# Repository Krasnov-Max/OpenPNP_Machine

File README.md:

# OpenPNP_Machine

Pick and Place small machine. 

Making parts machine if FreeCAD
Add configure files for RepRap firmware and OpenPNP

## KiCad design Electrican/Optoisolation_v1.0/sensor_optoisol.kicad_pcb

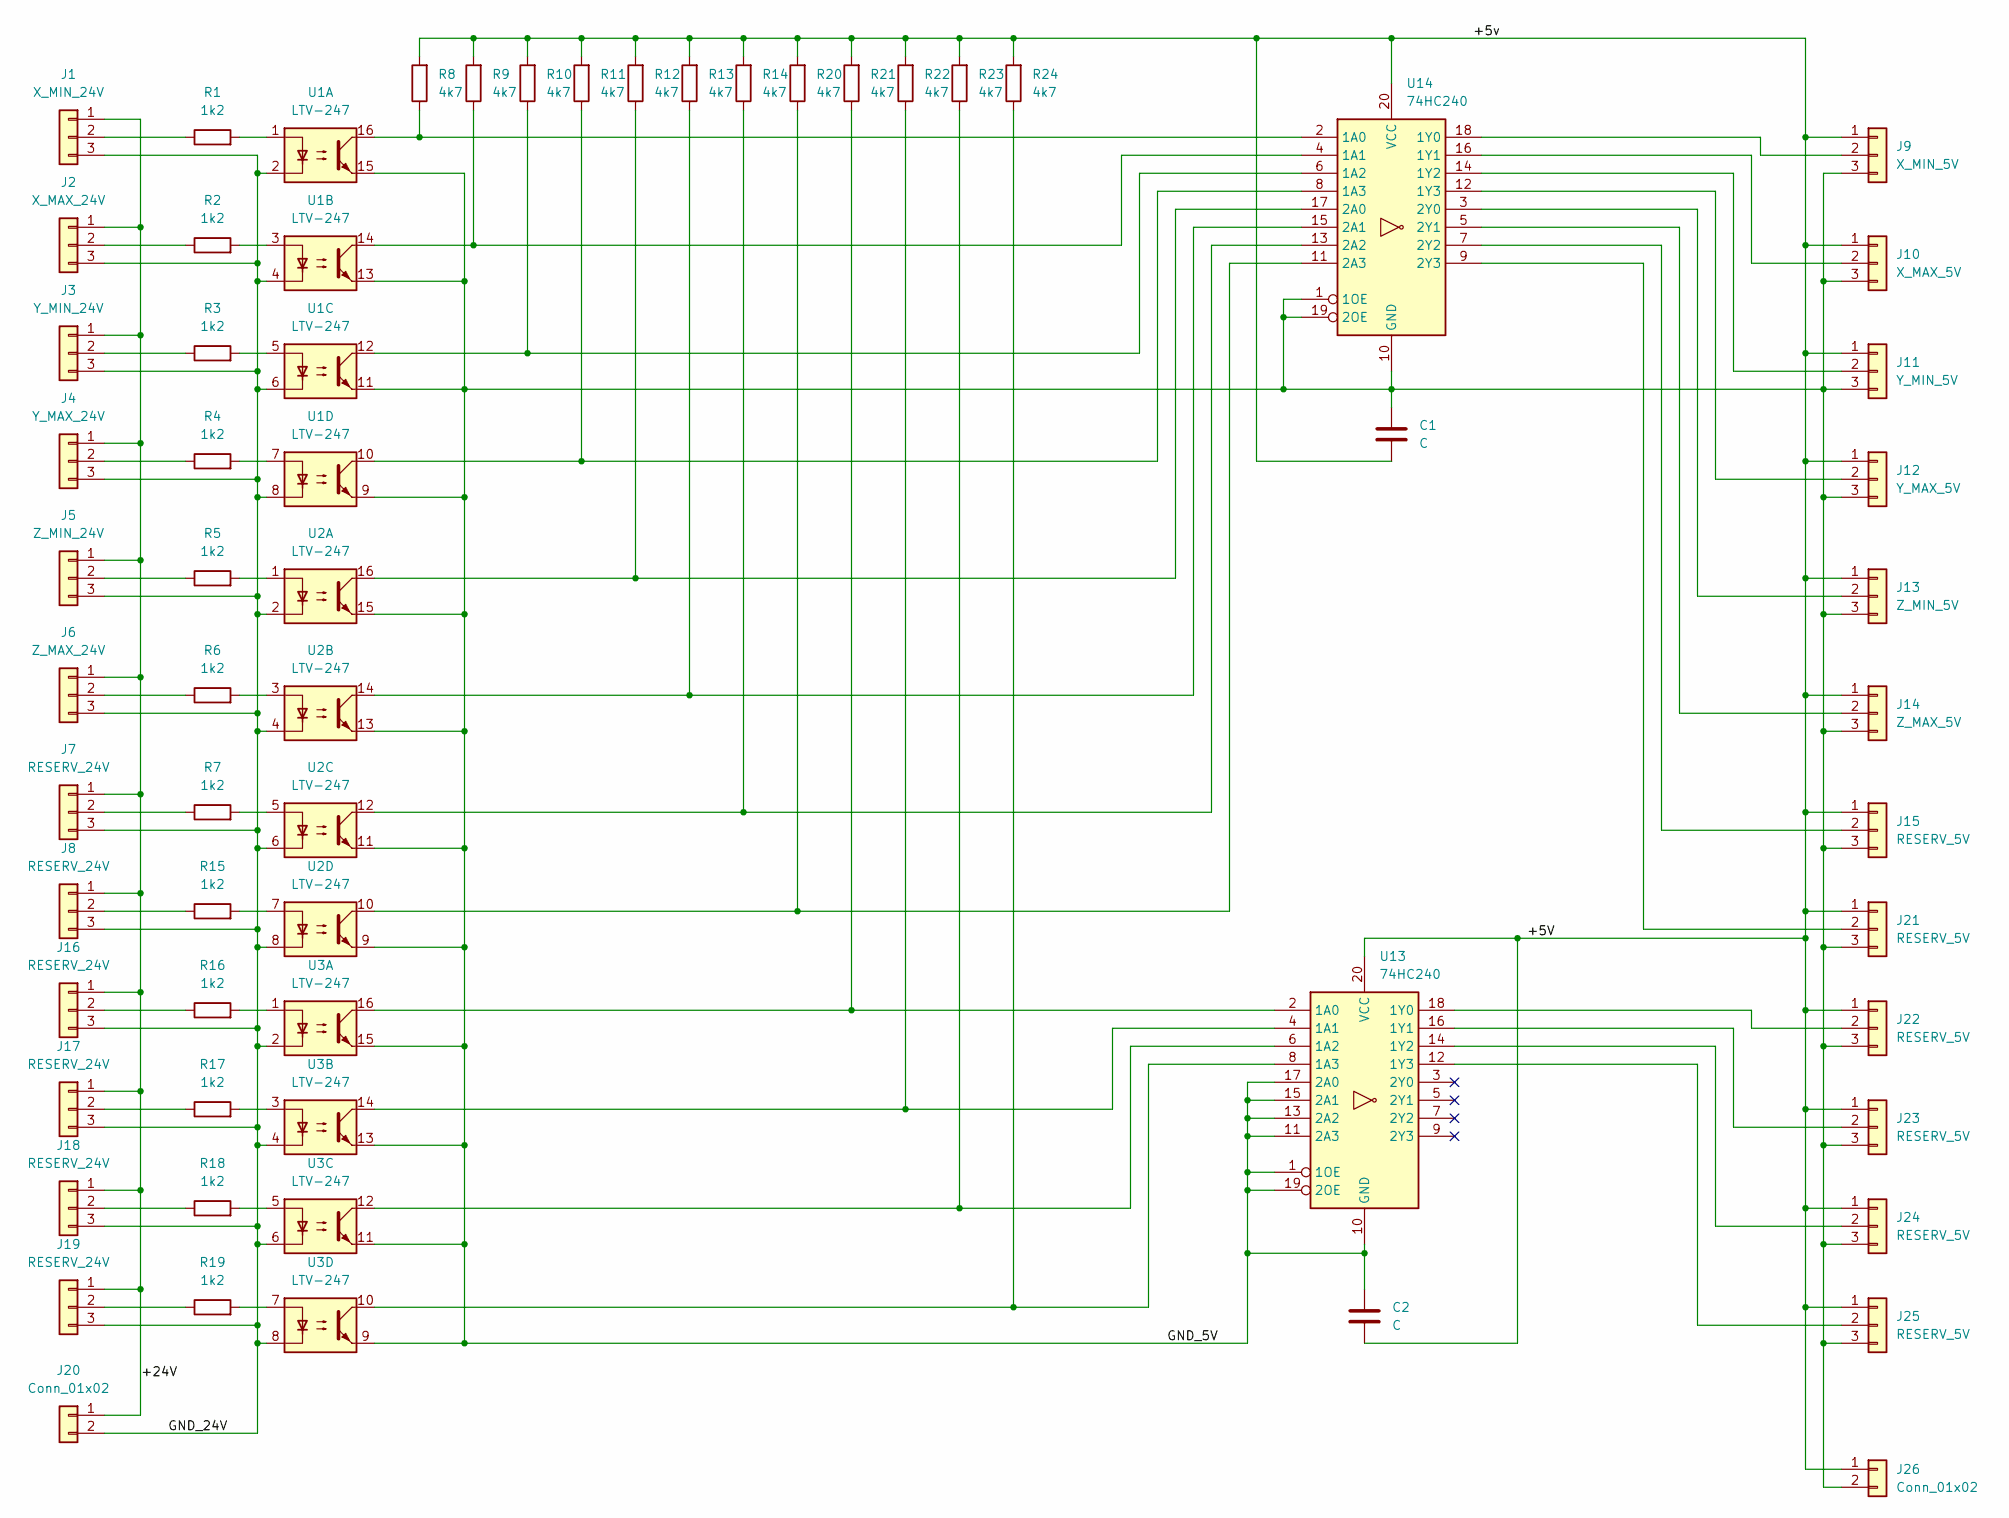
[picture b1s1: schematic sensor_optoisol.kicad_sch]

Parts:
C1, C2: C; C_0805_2012Metric
J1: Conn_01x03; Molex_SL_171971-0003_1x03_P2.54mm_Vertical
J2: X_MAX_24V; Molex_SL_171971-0003_1x03_P2.54mm_Vertical
J3: Y_MIN_24V; Molex_SL_171971-0003_1x03_P2.54mm_Vertical
J4: Y_MAX_24V; Molex_SL_171971-0003_1x03_P2.54mm_Vertical
J5: Z_MIN_24V; Molex_SL_171971-0003_1x03_P2.54mm_Vertical
J6: Z_MAX_24V; Molex_SL_171971-0003_1x03_P2.54mm_Vertical
J7, J8, J16, J17, J18, J19: RESERV_24V; Molex_SL_171971-0003_1x03_P2.54mm_Vertical
J9: X_MIN_5V; Molex_SL_171971-0003_1x03_P2.54mm_Vertical
J10: X_MAX_5V; Molex_SL_171971-0003_1x03_P2.54mm_Vertical
J11: Y_MIN_5V; Molex_SL_171971-0003_1x03_P2.54mm_Vertical
J12: Y_MAX_5V; Molex_SL_171971-0003_1x03_P2.54mm_Vertical
J13: Z_MIN_5V; Molex_SL_171971-0003_1x03_P2.54mm_Vertical
J14: Z_MAX_5V; Molex_SL_171971-0003_1x03_P2.54mm_Vertical
J15, J21, J22, J23, J24, J25: RESERV_5V; Molex_SL_171971-0003_1x03_P2.54mm_Vertical
J20, J26: Conn_01x02; Molex_SL_171971-0002_1x02_P2.54mm_Vertical
R1, R2, R3, R4, R5, R6, R7, R15, R16, R17, R18, R19: 1k2; R_0805_2012Metric_Pad1.20x1.40mm_HandSolder
R8, R9, R10, R11, R12, R13, R14, R20, R21, R22, R23, R24: 4k7; R_0805_2012Metric_Pad1.20x1.40mm_HandSolder
U1, U2, U3: LTV-247; SOIC-16W_5.3x10.2mm_P1.27mm
U13, U14: 74HC240; SOIC-20W_7.5x12.8mm_P1.27mm

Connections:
/+5V: C1.2, C2.2, J9.1, J10.1, J11.1, J12.1, J13.1, J14.1, J15.1, J21.1, J22.1, J23.1, J24.1, J25.1, J26.1, R8.2, R9.2, R10.2, R11.2, R12.2, R13.2, R14.2, R20.2, R21.2, R22.2, R23.2, R24.2, U13.20 (VCC), U14.20 (VCC)
/+24V: J1.1, J2.1, J3.1, J4.1, J5.1, J6.1, J7.1, J8.1, J16.1, J17.1, J18.1, J19.1, J20.1
/GND_5V: C1.1, C2.1, J9.3, J10.3, J11.3, J12.3, J13.3, J14.3, J15.3, J21.3, J22.3, J23.3, J24.3, J25.3, J26.2, U1.9, U1.11, U1.13, U1.15, U2.9, U2.11, U2.13, U2.15, U3.9, U3.11, U3.13, U3.15, U13.1 (1OE), U13.10 (GND), U13.11 (2A3), U13.13 (2A2), U13.15 (2A1), U13.17 (2A0), U13.19 (2OE), U14.1 (1OE), U14.10 (GND), U14.19 (2OE)
/GND_24V: J1.3, J2.3, J3.3, J4.3, J5.3, J6.3, J7.3, J8.3, J16.3, J17.3, J18.3, J19.3, J20.2, U1.2, U1.4, U1.6, U1.8, U2.2, U2.4, U2.6, U2.8, U3.2, U3.4, U3.6, U3.8
unnamed: J1.2, R1.1
unnamed: J2.2, R2.1
unnamed: J3.2, R3.1
unnamed: J4.2, R4.1
unnamed: J5.2, R5.1
unnamed: J6.2, R6.1
unnamed: J7.2, R7.1
unnamed: J8.2, R15.1
unnamed: J9.2, U14.18 (1Y0)
unnamed: J10.2, U14.16 (1Y1)
unnamed: J11.2, U14.14 (1Y2)
unnamed: J12.2, U14.12 (1Y3)
unnamed: J13.2, U14.3 (2Y0)
unnamed: J14.2, U14.5 (2Y1)
unnamed: J15.2, U14.7 (2Y2)
unnamed: J16.2, R16.1
unnamed: J17.2, R17.1
unnamed: J18.2, R18.1
unnamed: J19.2, R19.1
unnamed: J21.2, U14.9 (2Y3)
unnamed: J22.2, U13.18 (1Y0)
unnamed: J23.2, U13.16 (1Y1)
unnamed: J24.2, U13.14 (1Y2)
unnamed: J25.2, U13.12 (1Y3)
unnamed: R1.2, U1.1
unnamed: R2.2, U1.3
unnamed: R3.2, U1.5
unnamed: R4.2, U1.7
unnamed: R5.2, U2.1
unnamed: R6.2, U2.3
unnamed: R7.2, U2.5
unnamed: R8.1, U1.16, U14.2 (1A0)
unnamed: R9.1, U1.14, U14.4 (1A1)
unnamed: R10.1, U1.12, U14.6 (1A2)
unnamed: R11.1, U1.10, U14.8 (1A3)
unnamed: R12.1, U2.16, U14.17 (2A0)
unnamed: R13.1, U2.14, U14.15 (2A1)
unnamed: R14.1, U2.12, U14.13 (2A2)
unnamed: R15.2, U2.7
unnamed: R16.2, U3.1
unnamed: R17.2, U3.3
unnamed: R18.2, U3.5
unnamed: R19.2, U3.7
unnamed: R20.1, U2.10, U14.11 (2A3)
unnamed: R21.1, U3.16, U13.2 (1A0)
unnamed: R22.1, U3.14, U13.4 (1A1)
unnamed: R23.1, U3.12, U13.6 (1A2)
unnamed: R24.1, U3.10, U13.8 (1A3)

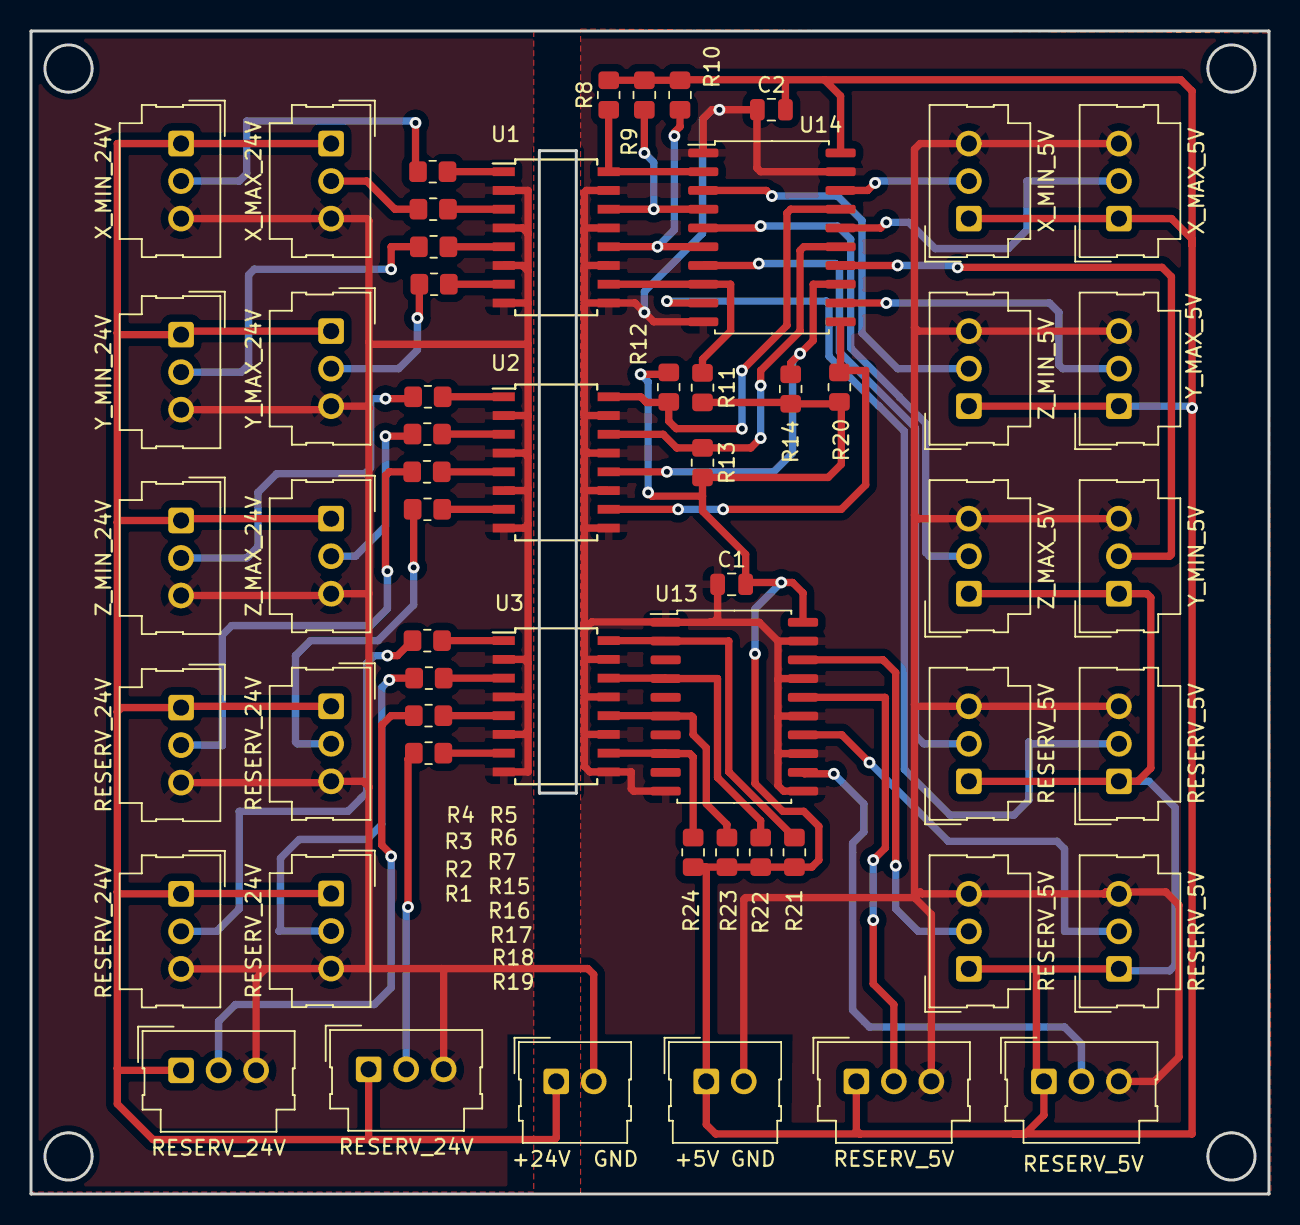
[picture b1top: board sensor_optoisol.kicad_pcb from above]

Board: 2 copper layers, 83.8 x 78.7 mm, 57 parts (0 on the bottom side), 52 nets.

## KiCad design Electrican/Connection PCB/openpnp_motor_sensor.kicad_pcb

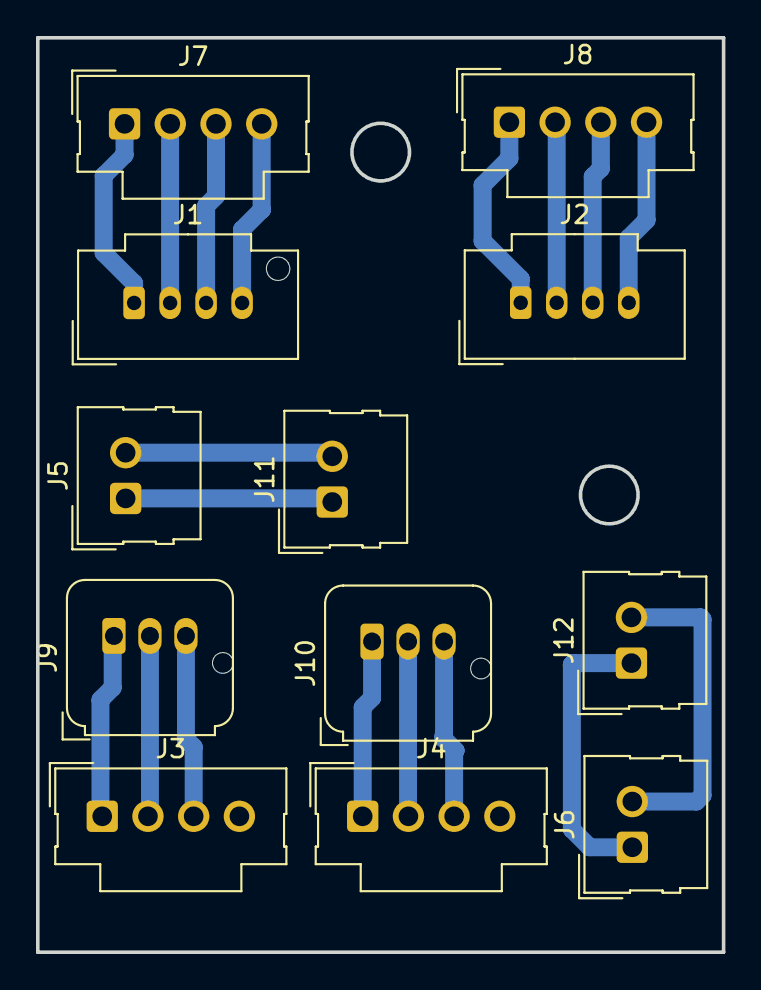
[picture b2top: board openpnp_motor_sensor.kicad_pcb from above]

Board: 2 copper layers, 38.1 x 50.8 mm, 12 parts (0 on the bottom side), 16 nets.

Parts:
J1: Conn_01x04; Molex_MicroClasp_55932-0410_1x04_P2.00mm_Vertical
J2: Conn_01x04; Molex_MicroClasp_55932-0430_1x04_P2.00mm_Vertical
J3, J4, J7, J8: Conn_01x04; Molex_SL_171971-0004_1x04_P2.54mm_Vertical
J5, J6, J11, J12: Conn_01x02; Molex_SL_171971-0002_1x02_P2.54mm_Vertical
J9, J10: Conn_01x04; JST_JWPF_B03B-JWPF-SK-R_1x03_P2.00mm_Vertical

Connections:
/+24 V: J3.1, J4.1, J9.1, J10.1
/A_E+: J2.1, J8.1
/A_E-: J2.2, J8.2
/A_Z+: J1.1, J7.1
/A_Z-: J1.2, J7.2
/B_E+: J2.3, J8.3
/B_E-: J2.4, J8.4
/B_Z+: J1.3, J7.3
/B_Z-: J1.4, J7.4
/GND Sensor: J3.2, J4.2, J9.2, J10.2
/Light +: J6.1, J12.1
/Light -: J6.2, J12.2
/Vacum +: J5.1, J11.1
/Vacum -: J5.2, J11.2
/Z Sensor down: J4.3, J10.3
/Z Sensor home: J3.3, J9.3

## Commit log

2022-05-05 Pick and Plase small machine
2022-05-25 Модель установки отриссовываеться во FreeCad. Add Y axis bulding
2022-06-02 Add Frame assenbly. Redisaine y axis.
2022-06-09 New version X axis leg rigt and left side Add assembly Y axis Add assembly frame machine
2022-06-09 Edit README file
2022-08-18 Final version
2022-10-10 New versionf final
2022-11-25 Remove stl files. Add new holder nema 8 motor. Add firmware reprap and config files. Add config files for OpenPnP software.
2022-11-25 Add electrical shematics kicad files.
2022-11-25 Change demension diwn cam holder
